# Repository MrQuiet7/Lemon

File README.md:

# Lemon! 🍋

### Stereo 20-LED VU Meter

> When life gives you a lemon, plug your music into it.

### Lemon is a compact stereo VU meter built around two LM3915N-1 LED bar-graph driver ICs.

### The design provides 10 LED levels for each stereo channel, giving a total of 20 LEDs. It is intended to be used as a standalone audio visualizer or integrated into an amplifier.

## Features

* Stereo audio level display
* 2× LM3915N-1
* 20× rectangular LEDs
* 10 levels per channel
* Independent sensitivity adjustment for left and right channels
* 3.5 mm stereo audio input/output
* Adjustable DOT / BAR display mode
* 15–25 V DC supply
* Designed for integration into an audio amplifier
* Two-layer PCB with large GND copper zones

## Design

* Lemon is based on the LED VU meter circuit published by Elliott Sound Products.

* The original circuit uses an LM3915 to drive ten LEDs according to the level of an incoming audio signal. Lemon uses two identical sections for the left and right channels.

* Each channel has its own sensitivity adjustment, allowing the two VU meters to be calibrated independently.

## Signal Flow

* The audio signal is passed through the board while each stereo channel is sampled by its respective LM3915 section for visual level indication.

## Power

* Lemon is designed for a 15–25 V DC supply.

* The PCB uses a single positive supply and ground connection. The LED supply path and LM3915 supply path are separated on the board according to the original circuit.

* The EARTH connection is kept separate from the main GND plane through the original 10 Ω connection, allowing the board to be integrated into a larger amplifier system without unnecessarily tying the two together.

## PCB

#### The PCB was designed in KiCad with a focus on:

* Clean stereo symmetry
* Short and organized signal paths
* Large GND copper zones
* Easy component identification
* Through-hole construction
* Simple integration into an amplifier enclosure

### The two rows of LEDs form the main visual element of the board, with the LM3915 circuits and adjustment controls positioned behind them.

* Components

### Quantity	Component
* 2	x LM3915N-1
* 20 x	Rectangular LEDs
* 2	x 50 kΩ potentiometers
* 2	x 3.5 mm stereo TRS jacks
* 2	x 82 Ω / 0.5 W resistors
* 2	x 1.2 kΩ resistors
* 2 x	2.2 kΩ resistors
* 2	x 10 kΩ resistors
* 2	x 10 Ω resistors
* 4	x 100 nF capacitors

### Component values and quantities should be verified against the final schematic and BOM before assembly.

## Project Status

* The VU meter circuit is based on the design published by [Elliott Sound Products](https://sound-au.com/project60.htm).

* Lemon is an independent PCB implementation and stereo adaptation of the circuit, with a custom PCB layout, mechanical arrangement, and visual design.

## License

#### GNU General Public License v3.0

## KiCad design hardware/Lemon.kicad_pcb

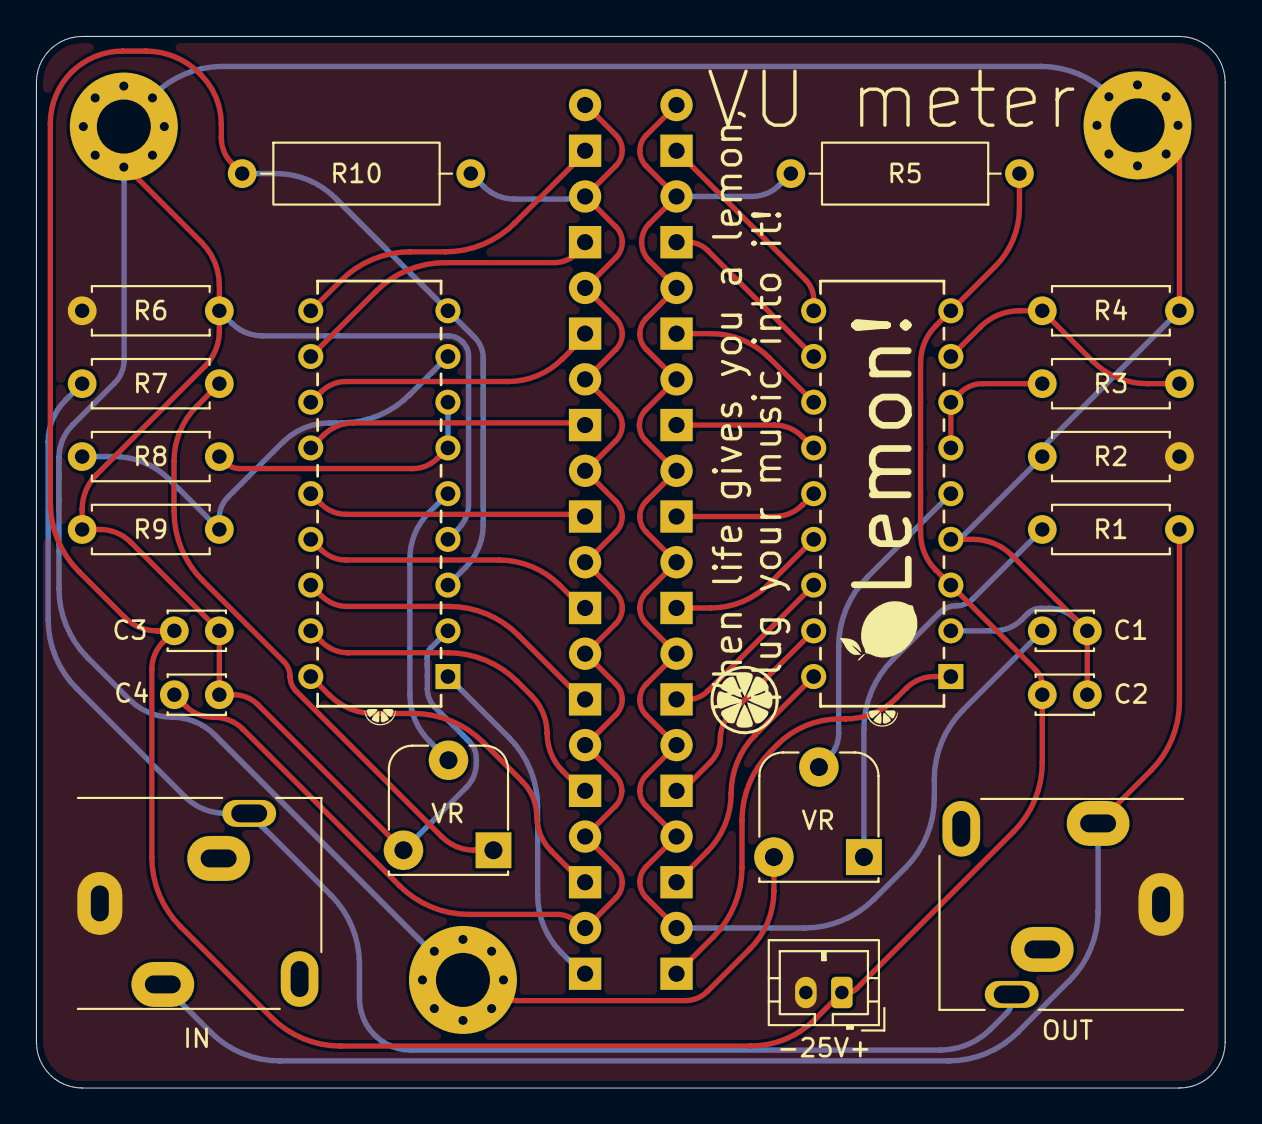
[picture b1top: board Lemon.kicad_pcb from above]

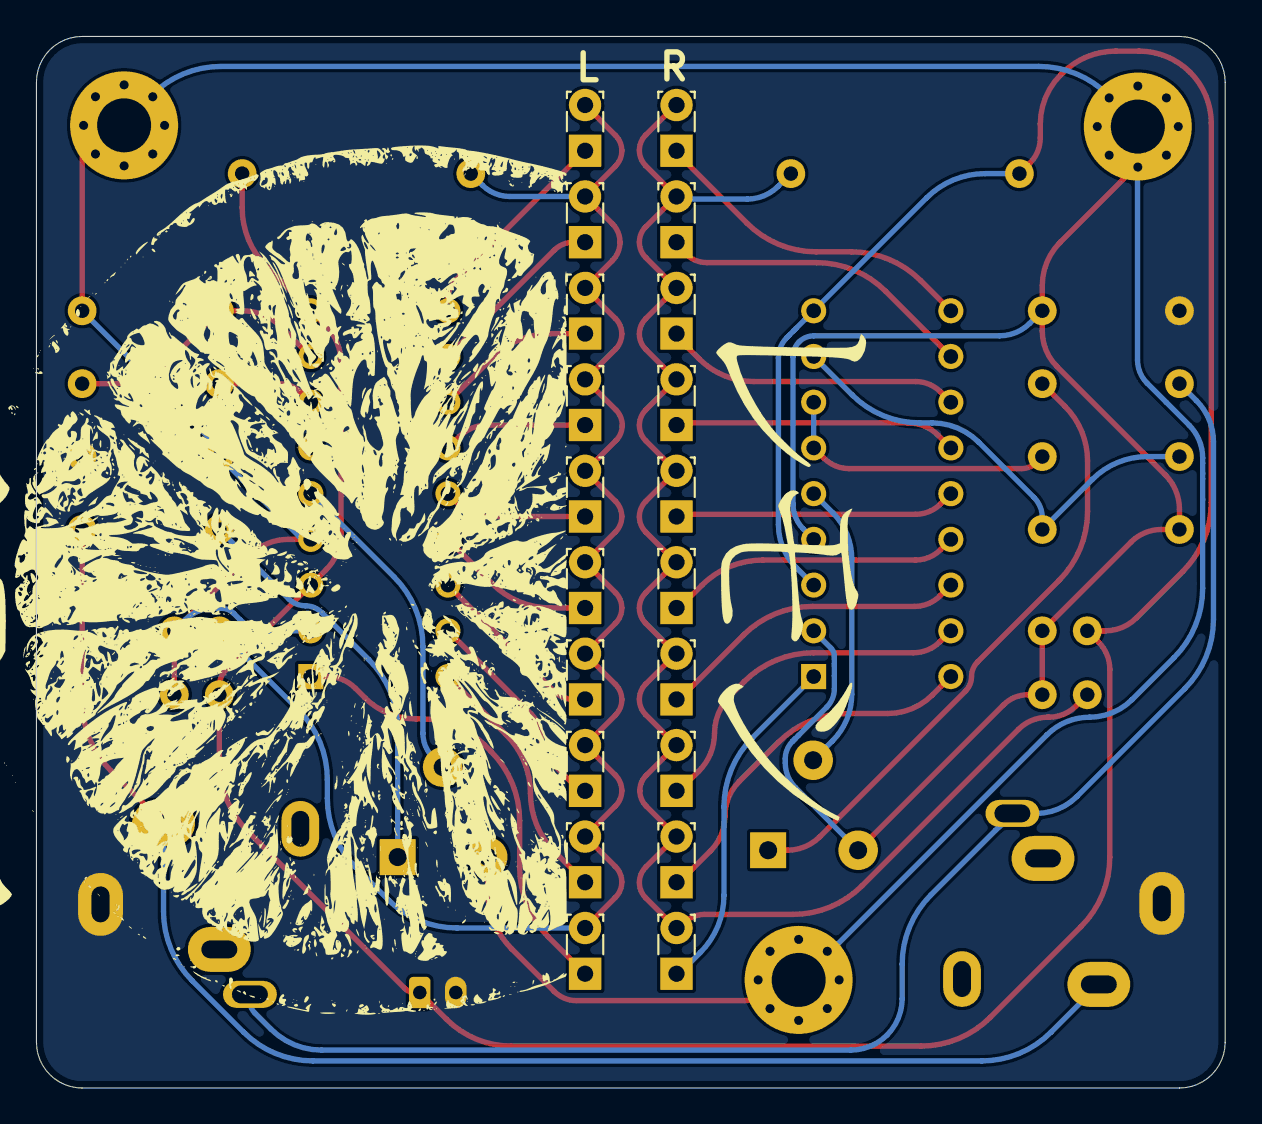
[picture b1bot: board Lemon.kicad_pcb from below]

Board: 2 copper layers, 66.0 x 58.4 mm, 41 parts (20 on the bottom side), 35 nets.

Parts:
-25V+: 25v; JST_PH_B2B-PH-K_1x02_P2.00mm_Vertical
C1, C2, C3, C4: 100n; C_Disc_D3.0mm_W2.0mm_P2.50mm
D1, D2, D3, D4, D5, D6, D7, D8, D9, D10, D11, D12, D13, D14, D15, D16, D17, D18, D19, D20: LED; LED_Rectangular_W3.9mm_H1.9mm
IN: AudioJack3_SwitchTR; Jack_3.5mm_CUI_SJ1-3515N_Horizontal
OUT: AudioJack3_SwitchTR; Jack_3.5mm_CUI_SJ1-3515N_Horizontal
R1, R2, R6, R7: 10k; R_Axial_DIN0207_L6.3mm_D2.5mm_P7.62mm_Horizontal
R3, R8: 1.2k; R_Axial_DIN0207_L6.3mm_D2.5mm_P7.62mm_Horizontal
R4, R9: 2.2k; R_Axial_DIN0207_L6.3mm_D2.5mm_P7.62mm_Horizontal
R5, R10: 82R0.5W; R_Axial_DIN0309_L9.0mm_D3.2mm_P12.70mm_Horizontal
U1, U2: LM3915N-1; NA18A_TEX
VR: 50k; Potentiometer_RM065
VR#2: 50k; Potentiometer_RM065

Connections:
/6: R3.2, U1.6 (DIVIDER(HIGH_END)), U1.7 (REFERENCE_OUTPUT)
/8: R3.1, R4.2, U1.8 (REFERENCE_ADJUST)
/GND: -25V+.2, IN.S, OUT.S, R2.1, R6.1
/L: IN.T, OUT.T, R1.1
/LED1: D1.1 (K), U1.1 (LED_NO_1)
/LED2: D2.1 (K), U1.18 (LED_NO_2)
/LED3: D3.1 (K), U1.17 (LED_NO_3)
/LED4: D4.1 (K), U1.16 (LED_NO_4)
/LED5: D5.1 (K), U1.15 (LED_NO_5)
/LED6: D6.1 (K), U1.14 (LED_NO_6)
/LED7: D7.1 (K), U1.13 (LED_NO_7)
/LED8: D8.1 (K), U1.12 (LED_NO_8)
/LED9: D9.1 (K), U1.11 (LED_NO_9)
/LED10: D10.1 (K), U1.10 (LED_NO_10)
/LED11: D11.1 (K), U2.1 (LED_NO_1)
/LED12: D12.1 (K), U2.18 (LED_NO_2)
/LED13: D13.1 (K), U2.17 (LED_NO_3)
/LED14: D14.1 (K), U2.16 (LED_NO_4)
/LED15: D15.1 (K), U2.15 (LED_NO_5)
/LED16: D16.1 (K), U2.14 (LED_NO_6)
/LED17: D17.1 (K), U2.13 (LED_NO_7)
/LED18: D18.1 (K), U2.12 (LED_NO_8)
/LED19: D19.1 (K), U2.11 (LED_NO_9)
/LED20: D20.1 (K), U2.10 (LED_NO_10)
/Lin: U2.5 (SIGNAL_INPUT), VR#2.2
/R: IN.R, OUT.R, R7.1
/Rin: U1.5 (SIGNAL_INPUT), VR.2
/VCC: -25V+.1, C2.1, C3.1, R5.1, R10.1, U1.3 (V+), U1.9 (MODE_SELECT), U2.3 (V+), U2.9 (MODE_SELECT)
/g: R8.1, R9.2, U2.8 (REFERENCE_ADJUST)
/s: R8.2, U2.6 (DIVIDER(HIGH_END)), U2.7 (REFERENCE_OUTPUT)
Earth: C1.2, C2.2, C3.2, C4.2, R2.2, R4.1, R6.2, R9.1, U1.2 (V-), U1.4 (DIVIDER(LOW_END)), U2.2 (V-), U2.4 (DIVIDER(LOW_END)), VR.3, VR#2.3
unnamed: C1.1, D1.2 (A), D2.2 (A), D3.2 (A), D4.2 (A), D5.2 (A), D6.2 (A), D7.2 (A), D8.2 (A), D9.2 (A), D10.2 (A), R5.2
unnamed: C4.1, D11.2 (A), D12.2 (A), D13.2 (A), D14.2 (A), D15.2 (A), D16.2 (A), D17.2 (A), D18.2 (A), D19.2 (A), D20.2 (A), R10.2
unnamed: R1.2, VR.1
unnamed: R7.2, VR#2.1
